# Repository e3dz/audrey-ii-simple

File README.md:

# Audrey II

Audrey II is a droning horroscape generator instrument for the Daisy Seed + SynthUX Simple platform
based on simple physical modeling principles.

_The vortex beckons you. With trembling fingers, you ever so gently turn the mysterious knob within.
Gently, at first, the engine stirs and the arcane beast within awakens. Your pulse quickens.
It wants more. As you turn the knob further, a chilling draft fills the room. The tone swells.
You attempt to appease it with the other controls, but its cries merely evolve into something new,
 equally terrifying and beautiful. A tear rolls down your cheek. The prophecy is fulfilled._

## Overview

At the core of Audrey II is a [Karplus Strong](https://en.wikipedia.org/wiki/Karplus%E2%80%93Strong_string_synthesis)
string model, one of simplest  possible string-waveguide physical modeling implementations.

The output tap of the string model feeds into a soft-clipping distortion, then a reverb,
then into fairly gentle linear lowpass and highpass EQ filters, and then finally into a
longer delay line (aka "body") before being fed back into the string model.

Rather than the typical noise burst or other excitation signals used in "realistic" K-S
models, Audrey-II simply feeds the string a constant stream of inaudible white noise.
As a result, no sound is produced by the instrument until the outer feedback gain is increased
(the big knob with all the circles around it).

This causes the aforementioned feedback loop to activate and a signal begins to build. The
rough fundamental pitch of the sound is determined by the K-S string delay line length
("frequency") and the overtones which resonate and the overall timbre of the sound is
determined by the rest of the controls in the outer feedback loop.

Finally, the output of this section goes through a tape-like delay with a fairly long
maximum delay time and a feedback control designed to deliberately produce infinitely
growing/saturating feedback, for creative distorted warping and warbling possibilities.

## Flashing the Daisy Seed

The easiest way to program an assembled Audrey II is with a pre-built binary file.
This does not require setting up the toolchain or compiling any code.

1. Download the latest `.bin` file from the [releases page](https://github.com/infrasonicaudio/audrey-ii-simple/releases)
2. Go to the [Daisy Web Programmer](https://electro-smith.github.io/Programmer/) in Google Chrome
3. Connect the Daisy Seed to your computer with a USB cable (double check that the cable you use actually carries data, not just power)
4. Follow the Help instructions at the top to put the Daisy Seed into bootloader mode and connect it to the web programmer
5. In the section labeled "Or select a file from your computer..." click "Browse" and open the `.bin` file you downloaded in step 1
6. At the bottom click "Program" and wait for the process to complete

## Firmware Hacking

1. Install the [Daisy Toolchain](https://github.com/electro-smith/DaisyWiki/wiki/1.-Setting-Up-Your-Development-Environment#1-install-the-toolchain) for your operating system
2. Clone this repository and its submodules
3. Open the repository folder in VScode
4. Run the "build_all" task (see: [VSCode tasks](https://code.visualstudio.com/Docs/editor/tasks)). You only have to build_all once to ensure the libraries are built, after that you can do just "build"
5. After a successful build you can flash the Seed using the "program" or "program-dfu" task depending on whether you're using an STLink or DFU over USB

Or if you don't want to use VSCode, you can run standard gnu `make` in the root of `lib/libDaisy`,
`lib/DaisySp` and finally in the repository root. Then you can use `make program` or
`make program-dfu` to flash the built binary.

## License

This project is licensed under the MIT License. See `LICENSE` for details.

This project uses code from DaisySP, libDaisy, RtMidi, and RtAudio which are all
also licensed under the MIT license. The relevant license documentation and
source code for these can be found in `lib/` as git submodules.

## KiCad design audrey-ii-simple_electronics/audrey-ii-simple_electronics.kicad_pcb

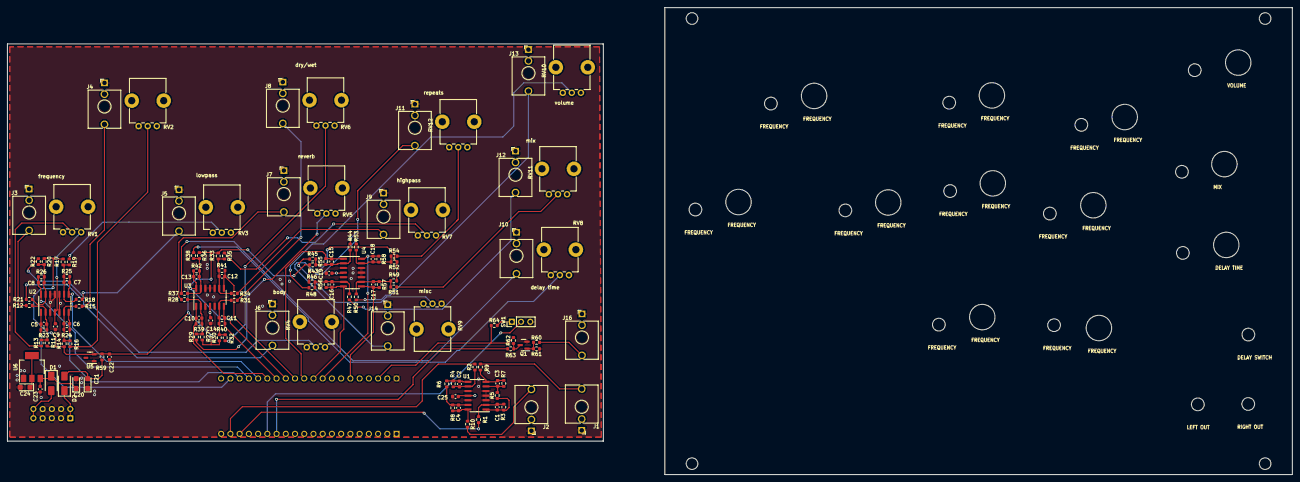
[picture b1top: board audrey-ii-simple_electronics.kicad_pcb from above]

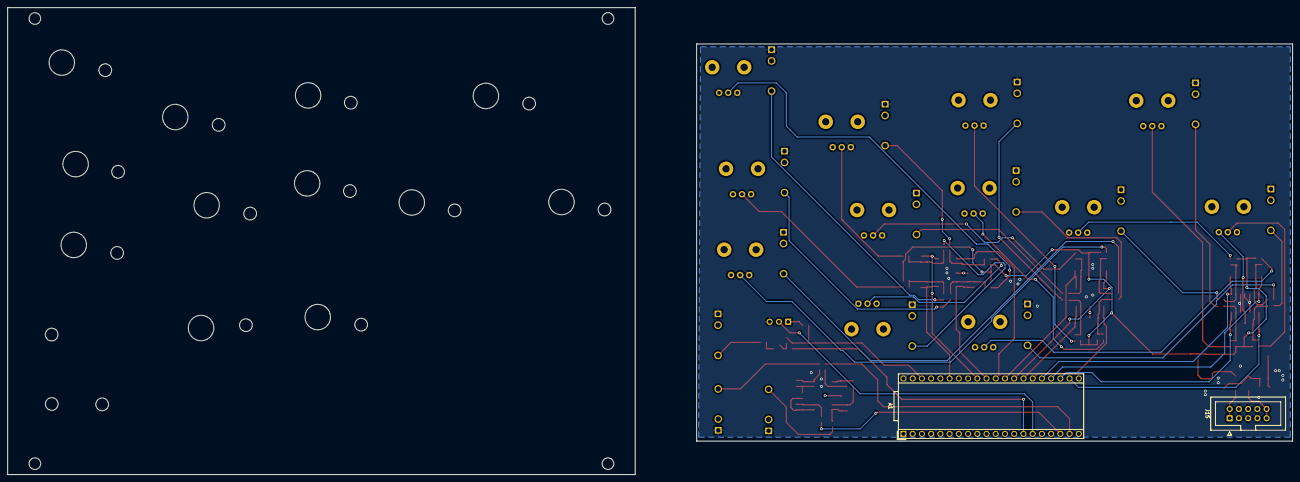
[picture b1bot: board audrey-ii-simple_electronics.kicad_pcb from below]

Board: 4 copper layers, 353.6 x 128.5 mm, 128 parts (2 on the bottom side), 75 nets.

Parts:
A1: Electrosmith_Daisy_Seed_Rev4; Electrosmith_Daisy_Seed
C1, C2, C3, C4: 47p; C_0603_1608Metric
C5, C6, C7, C8, C10, C11, C12, C13, C15, C16, C17, C18: 10n; C_0603_1608Metric
C9, C14, C19, C22, C23, C25: 100n; C_0603_1608Metric
C20, C21: 22u; CP_EIA-3216-18_Kemet-A
C24: 10uF; CP_EIA-3216-18_Kemet-A
D1, D2: D_Small; D_SMA
J1, J2, J16: DAC_OUT_2; Jack_3.5mm_QingPu_WQP-PJ398SM_Vertical_CircularHoles
J3, J7, J11: CV_1; Jack_3.5mm_QingPu_WQP-PJ398SM_Vertical_CircularHoles
J4, J8, J12: CV_2; Jack_3.5mm_QingPu_WQP-PJ398SM_Vertical_CircularHoles
J5, J9, J13: CV_3; Jack_3.5mm_QingPu_WQP-PJ398SM_Vertical_CircularHoles
J6, J10, J14: CV_4; Jack_3.5mm_QingPu_WQP-PJ398SM_Vertical_CircularHoles
J15: Conn_02x05_Odd_Even; IDC-Header_2x05_P2.54mm_Vertical
Q1: MMBT3904; SOT-23
R1, R2, R62: 10k; R_0603_1608Metric
R3, R4, R5, R6, R7, R8, R12, R15, R18, R21, R28, R31, R34, R37, R44, R47, R50, R53, R60: 100k; R_0603_1608Metric
R9, R10, R63, R64: 1k; R_0603_1608Metric
R11, R14, R17, R20, R27, R30, R33, R36, R43, R46, R49, R52: 200k; R_0603_1608Metric
R13, R16, R19, R22, R23, R24, R25, R26, R29, R32, R35, R38, R39, R40, R41, R42, R45, R48, R51, R54, R55, R56, R57, R58: 66k5; R_0603_1608Metric
R59: 2k; R_0603_1608Metric
R61: 1M; R_0603_1608Metric
RV1, RV2, RV3, RV4, RV5, RV6, RV7, RV8, RV9, RV10, RV11, RV12: M-10K-B-D; Potentiometer_Alps_RK09K_Single_Vertical
SW1: SW_SPDT; PinHeader_1x03_P2.54mm_Vertical
U1: TL074; SOIC-14_3.9x8.7mm_P1.27mm
U2, U3, U4: MCP6004; SOIC-14_3.9x8.7mm_P1.27mm
U5: LM4040-10V; SOT-23-3
U6: LD1117S50TR_SOT223; SOT-223-3_TabPin2

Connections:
+3.3V: A1.38 (3V3_D), R62.2, R64.1
+3.3VA: A1.21 (3V3_A), C9.1, C14.1, C19.1, C25.1, RV1.1, RV2.1, RV3.1, RV4.1, RV5.1, RV6.1, RV7.1, RV8.1, RV9.1, RV10.1, RV11.1, RV12.1, U1.11 (V-), U2.4 (V+), U3.4 (V+), U4.4 (V+)
+5V: C24.1, U6.2 (VO)
-10V_REF: C22.1, R11.1, R14.1, R17.1, R20.1, R27.1, R30.1, R33.1, R36.1, R43.1, R46.1, R49.1, R52.1, R59.1, U5.2 (A)
/ADCBufferIn1/ADC_1: A1.26 (ADC_4), C10.1, R39.2, U3.1
/ADCBufferIn1/ADC_2: A1.27 (ADC_5), C11.1, R40.2, U3.7
/ADCBufferIn1/ADC_3: A1.29 (DAC_OUT2), C12.1, R41.2, U3.8
/ADCBufferIn1/ADC_4: A1.28 (ADC_6), C13.1, R42.2, U3.14
/ADCBufferIn1/KNOB_1: R29.1, RV5.2
/ADCBufferIn1/KNOB_2: R32.1, RV6.2
/ADCBufferIn1/KNOB_3: R35.1, RV7.2
/ADCBufferIn1/KNOB_4: R38.1, RV8.2
/ADCBufferIn2/ADC_1: A1.30 (DAC_OUT1), C15.1, R55.2, U4.1
/ADCBufferIn2/ADC_2: A1.31 (SAI2_MCLK), C16.1, R56.2, U4.7
/ADCBufferIn2/ADC_3: A1.35 (SAI2_SCK), C17.1, R57.2, U4.8
/ADCBufferIn2/ADC_4: A1.32 (SAI2_SD_B), C18.1, R58.2, U4.14
/ADCBufferIn2/KNOB_1: R45.1, RV9.2
/ADCBufferIn2/KNOB_2: R48.1, RV10.2
/ADCBufferIn2/KNOB_3: R51.1, RV11.2
/ADCBufferIn2/KNOB_4: R54.1, RV12.2
/ADCBufferIn/ADC_1: A1.22 (ADC_0), C5.1, R23.2, U2.1
/ADCBufferIn/ADC_2: A1.23 (ADC_1), C6.1, R24.2, U2.7
/ADCBufferIn/ADC_3: A1.25 (ADC_3), C7.1, R25.2, U2.8
/ADCBufferIn/ADC_4: A1.24 (ADC_2), C8.1, R26.2, U2.14
/ADCBufferIn/KNOB_1: R13.1, RV1.2
/ADCBufferIn/KNOB_2: R16.1, RV2.2
/ADCBufferIn/KNOB_3: R19.1, RV3.2
/ADCBufferIn/KNOB_4: R22.1, RV4.2
/Audio Buffer Out/AUDIO_OUT_L: A1.18 (AUDIO_OUT_1), R1.1
/Audio Buffer Out/AUDIO_OUT_R: A1.19 (AUDIO_OUT_2), R2.1
/GPIOIn/In: A1.14 (USART1_TX), R63.1
/SPDT/I/O: A1.15 (USART1_RX), SW1.2 (B)
GND: A1.20 (AGND), A1.40 (DGND), C9.2, C14.2, C19.2, C20.2, C21.1, C22.2, C23.2, C24.2, C25.2, J1.S, J2.S, J3.S, J4.S, J5.S, J6.S, J7.S, J8.S, J9.S, J10.S, J11.S, J12.S, J13.S, J14.S, J15.3, J15.4, J15.5, J15.6, J15.7, J15.8, J16.S, Q1.2 (E), R61.1, RV1.3, RV2.3, RV3.3, RV4.3, RV5.3, RV6.3, RV7.3, RV8.3, RV9.3, RV10.3, RV11.3, RV12.3, SW1.3 (C), U1.3 (+), U1.4 (V+), U1.5 (+), U1.10 (+), U1.12 (+), U2.3 (+), U2.5 (+), U2.10 (+), U2.11 (V-), U2.12 (+), U3.3 (+), U3.5 (+), U3.10 (+), U3.11 (V-), U3.12 (+), U4.3 (+), U4.5 (+), U4.10 (+), U4.11 (V-), U4.12 (+), U5.1 (K), U6.1 (GND)
unnamed: C1.1, R3.2, R5.1, U1.1
unnamed: C2.1, R4.2, R6.1, U1.8
unnamed: C3.1, R7.2, R9.1, U1.7
unnamed: C4.1, R8.2, R10.1, U1.14
unnamed: D1.2 (A), J15.9, J15.10
unnamed: D2.1 (K), J15.1, J15.2
unnamed: J1.T, R9.2
unnamed: J2.T, R10.2
unnamed: J3.T, R12.1
unnamed: J4.T, R15.1
unnamed: J5.T, R18.1
unnamed: J6.T, R21.1
unnamed: J7.T, R28.1
unnamed: J8.T, R31.1
unnamed: J9.T, R34.1
unnamed: J10.T, R37.1
unnamed: J11.T, R44.1
unnamed: J12.T, R47.1
unnamed: J13.T, R50.1
unnamed: J14.T, R53.1
unnamed: J16.T, R60.1
unnamed: Q1.1 (B), R60.2, R61.2
unnamed: Q1.3 (C), R62.1, R63.2
unnamed: R64.2, SW1.1 (A)
unnamed: C1.2, R1.2, R3.1, U1.2 (-)
unnamed: C3.2, R5.2, R7.1, U1.6 (-)
unnamed: C2.2, R2.2, R4.1, U1.9 (-)
unnamed: C4.2, R6.2, R8.1, U1.13 (-)
unnamed: C5.2, R11.2, R12.2, R13.2, R23.1, U2.2 (-)
unnamed: C6.2, R14.2, R15.2, R16.2, R24.1, U2.6 (-)
unnamed: C7.2, R17.2, R18.2, R19.2, R25.1, U2.9 (-)
unnamed: C8.2, R20.2, R21.2, R22.2, R26.1, U2.13 (-)
unnamed: C10.2, R27.2, R28.2, R29.2, R39.1, U3.2 (-)
unnamed: C11.2, R30.2, R31.2, R32.2, R40.1, U3.6 (-)
unnamed: C12.2, R33.2, R34.2, R35.2, R41.1, U3.9 (-)
unnamed: C13.2, R36.2, R37.2, R38.2, R42.1, U3.13 (-)
unnamed: C15.2, R43.2, R44.2, R45.2, R55.1, U4.2 (-)
unnamed: C16.2, R46.2, R47.2, R48.2, R56.1, U4.6 (-)
unnamed: C17.2, R49.2, R50.2, R51.2, R57.1, U4.9 (-)
unnamed: C18.2, R52.2, R53.2, R54.2, R58.1, U4.13 (-)
VCC: C20.1, C23.1, D1.1 (K), U6.3 (VI)
VEE: C21.2, D2.2 (A), R59.2

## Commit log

2022-07-25 Remove outdated comments
2022-08-14 Add -j8 to build program dfu task
2022-12-03 Update submodules
2022-12-03 Parameter mapping tweaks
2022-12-04 Add input signal to string excitation
2022-12-04 Use overdrive instead of softclip
2022-12-04 Whitespace cleanup
2022-12-04 Rework KarplusString for this patch
    - Fixed one pole frequency in feedback loop
    - Remove brightness/decay and compensation
2023-02-10 Invert t60 coef calculation
2023-02-10 Update submodule refs
2023-02-10 TODO comment and minor cleanup
2023-02-10 Add allocate_buf to SDRAM allocation methods
2023-02-11 Add reverb controls
2023-02-11 Revert "Invert t60 coef calculation"
    This reverts commit b7fa467e3ebee11b8872a6e8f61d2900d19f7c2a.
2023-02-11 Reverb controls adjustments
2023-03-21 Define pin numbers/params for SB version
2023-03-21 Add output volume control
2023-05-01 Add switch to half delay time (SB mapping)
2023-07-20 Remove macOS build and dependencies
2023-07-20 Fix intellisense and add windows config
2023-07-20 README update with build/flash docs
2023-07-20 Line break edit
2023-07-20 Add routing doc image
2023-07-24 Add build guide link to README
2023-10-31 added electronics
2023-11-04 front panel
